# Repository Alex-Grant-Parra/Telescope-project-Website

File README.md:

# SELENO - Automated Sidereal Tracking and Remote Astronomy

## A modern telescope automation system for remote observation, object tracking and astrophotography with a web-based observatory management platform.

---

## Features

* Web-based telescope control  
* Distributed telescope network management  
* Automated target acquisition and tracking  
* Astrophotography image capture  
* Observation scheduling and automation  
* Interactive planetarium interface  
* Astronomical object database  
* Solar system object tracking  
* Remote camera and mount control  
* REST API for astronomical data access  
* Raspberry Pi and ESP32 powered telescope nodes  
* Beginner-friendly operation with advanced manual controls  
* Source-available and self-hostable

## System Architecture

SELENO uses a web-based control server connected to distributed Raspberry Pi \+ ESP32 telescope nodes. Commands, live view camera frames, and tracking data flow through WebSocket channels, while each node handles its own motor control, sensors, and imaging pipeline.

## Client Setup (For running SELENO on your telescope system)

* In the email you were sent when you purchased the telescope system, select register. This will give you a client ID, API token and server URL.  
* Create an account, and link your client ID and API key to it, following the on screen directions.  
* Power on the system, and wait for the blue LED to stay constantly lit.  
* Use the keypad to enter in the client ID, API token and server URL. There will be an on screen confirmation when connected.  
* (Recommended) Check for updates in the settings window. This may take several minutes if updates are found. Do not power off your device.   
* Log in and access the main interface page. It is recommended that you follow the first time tutorial on how to use the site.

## ADVANCED - Server Setup (For running your own control server)

 * Follow this guide to learn how to do this:
 https://github.com/Alex-Grant-Parra/SELENO/wiki/Server-Setup-(For-running-your-own-control-server)

 ## Core Runtime Behavior

- Flask app boots from Server.py.
- Blueprints are auto-loaded from controllers/.
- SQLite database is stored at instance/Data.db.
- WebSocket services start with the app:
	- Command server: port 4000
	- LiveView server: port 8000
- Route list is auto-generated to templates/routes.txt at startup.

## Important Environment Variables

- FLASK_SECRET_KEY: Flask session secret
- ENCRYPTION_KEY: application encryption key
- FLASK_USE_SSL: enable Flask TLS mode (True/False)
- SSL_CERT_PATH, SSL_KEY_PATH: cert and key when FLASK_USE_SSL is enabled
- FLASK_SERVER_HOST, FLASK_SERVER_PORT: host/port display and overrides
- MAX_UPLOAD_BYTES: max upload size (default 128 MiB)
- WS_IP: WebSocket bind IP (default 0.0.0.0)
- WS_PING_INTERVAL, WS_PING_TIMEOUT: WebSocket keepalive settings
- TURNSTILE_SITE_KEY, TURNSTILE_SECRET_KEY: CAPTCHA support

## Planetary Models

SELENO includes a few different planetary models under the astrophysics folder, each with varying precision.
- V1_Keplarian is a traditional keplarian algorithm
- V2_VSOP87A is an iterative solution, taking the sum of a large number of orbital parameters
- V3_Helios is a custom N-body engine, with a local integrator and engine, with initial parameters provided by JPL SPICE data

## Notes

- instance/.env contains secrets and should not be committed.
- infrastructure/ contains deployment-related files and logs.
- When downloading the server, the database will not be included. This may change in future versions, but you will have to supply your own data for now.

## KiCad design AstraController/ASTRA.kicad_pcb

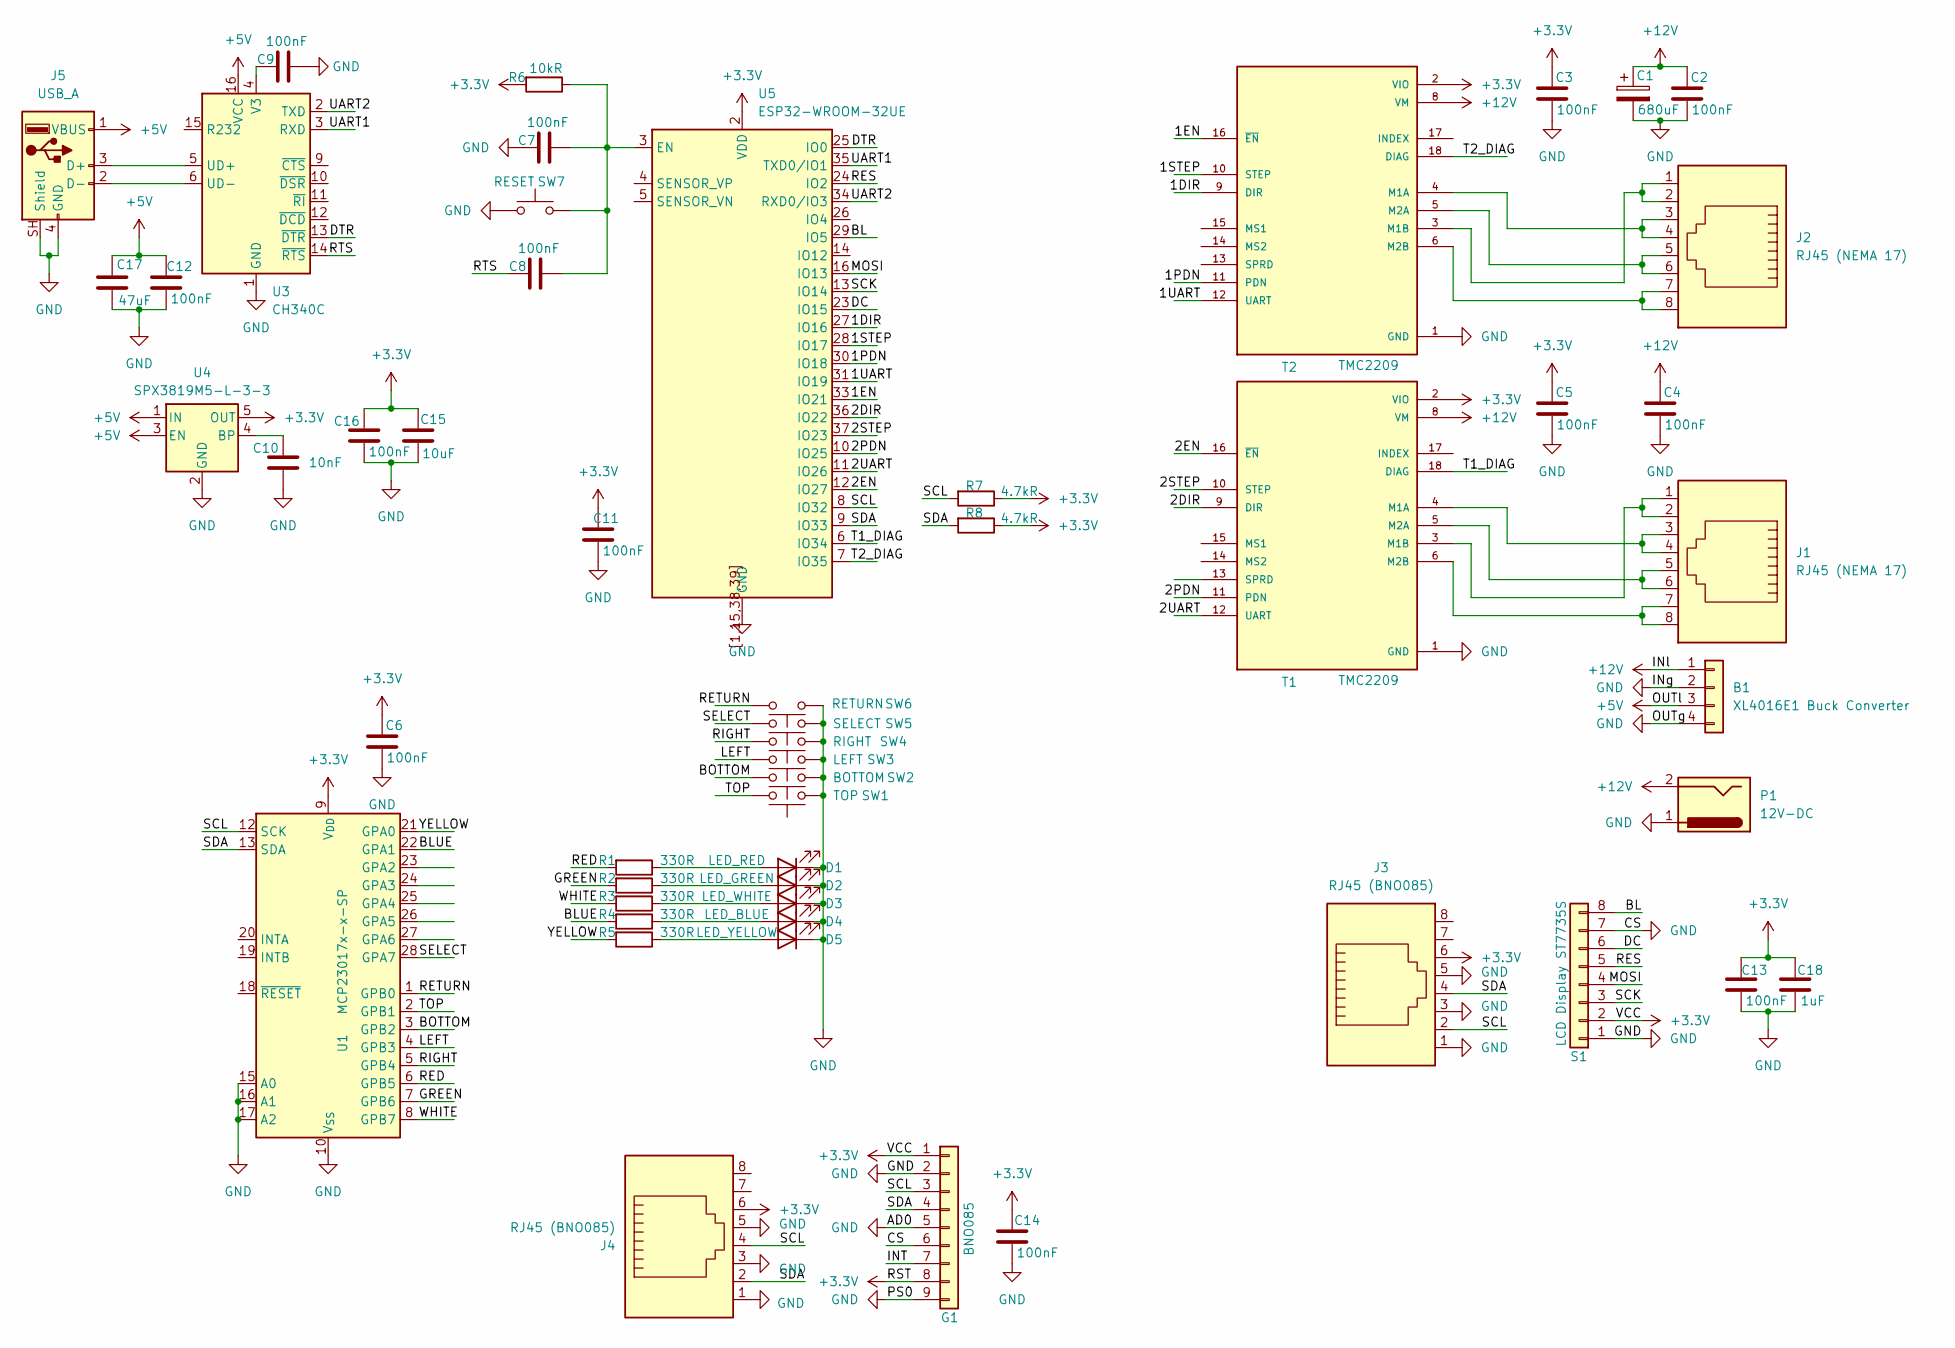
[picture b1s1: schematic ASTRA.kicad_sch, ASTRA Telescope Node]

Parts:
B1: XL4016E1 Buck Converter; Double 1x02 screw connector
C1: 680uF; CP_Radial_D10.0mm_P5.00mm
C2, C3, C4, C5, C6, C7, C8, C9, C11, C12, C13, C14, C16: 100nF; C_0402_1005Metric
C10: 10nF; C_0402_1005Metric
C15: 10uF; C_0402_1005Metric
C17: 47uF; C_1206_3216Metric
C18: 1uF; C_0402_1005Metric
D1: LED_RED; LED_0805_2012Metric
D2: LED_GREEN; LED_0805_2012Metric
D3: LED_WHITE; LED_0805_2012Metric
D4: LED_BLUE; LED_0805_2012Metric
D5: LED_YELLOW; LED_0805_2012Metric
G1: BNO085; PinSocket_1x09_P2.54mm_Vertical
J1, J2: RJ45 (NEMA 17); RJ45_Amphenol_54602-x08_Horizontal
J3, J4: RJ45 (BNO085); RJ45_Amphenol_54602-x08_Horizontal
J5: USB_A; USB_A_Connfly_DS1095
P1: 12V-DC; TerminalBlock_Xinya_XY308-2.54-2P_1x02_P2.54mm_Horizontal
R1, R2, R3, R4, R5: 330R; R_0402_1005Metric
R6: 10kR; R_0402_1005Metric
R7, R8: 4.7kR; R_0402_1005Metric
S1: LCD Display ST7735S; Quadruple 1x02 screw connector
SW1: TOP; TerminalBlock_Xinya_XY308-2.54-2P_1x02_P2.54mm_Horizontal
SW2: BOTTOM; TerminalBlock_Xinya_XY308-2.54-2P_1x02_P2.54mm_Horizontal
SW3: LEFT; TerminalBlock_Xinya_XY308-2.54-2P_1x02_P2.54mm_Horizontal
SW4: RIGHT; TerminalBlock_Xinya_XY308-2.54-2P_1x02_P2.54mm_Horizontal
SW5: SELECT; TerminalBlock_Xinya_XY308-2.54-2P_1x02_P2.54mm_Horizontal
SW6: RETURN; TerminalBlock_Xinya_XY308-2.54-2P_1x02_P2.54mm_Horizontal
SW7: RESET; TerminalBlock_Xinya_XY308-2.54-2P_1x02_P2.54mm_Horizontal
T1, T2: TMC2209; TMC2209module; PARTREV 1.20
U1: MCP23017x-x-SP; DIP-28_W7.62mm
U3: CH340C; SOIC-16_3.9x9.9mm_P1.27mm
U4: SPX3819M5-L-3-3; SOT-23-5; LCSC Part # C9055
U5: ESP32-WROOM-32UE

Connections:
+3.3V: C3.1, C5.1, C6.1, C11.1, C13.1, C14.1, C15.1, C16.1, C18.1, G1.1, G1.8, J3.6, J4.6, R6.2, R7.1, R8.1, S1.2, T1.2 (VIO), T2.2 (VIO), U1.9 (V_{DD}), U4.5 (OUT), U5.2 (VDD)
+5V: B1.3, C12.1, C17.1, J5.1 (VBUS), U3.16 (VCC), U4.1 (IN), U4.3 (EN)
+12V: B1.1, C1.1, C2.1, C4.1, P1.2, T1.8 (VM), T2.8 (VM)
/1DIR: T2.9 (DIR), U5.27 (IO16)
/1EN: T2.16 (~EN), U5.33 (IO21)
/1PDN: T2.11 (PDN), U5.30 (IO18)
/1STEP: T2.10 (STEP), U5.28 (IO17)
/1UART: T2.12 (UART), U5.31 (IO19)
/2DIR: T1.9 (DIR), U5.36 (IO22)
/2EN: T1.16 (~EN), U5.12 (IO27)
/2PDN: T1.11 (PDN), U5.10 (IO25)
/2STEP: T1.10 (STEP), U5.37 (IO23)
/2UART: T1.12 (UART), U5.11 (IO26)
/BL: S1.8, U5.29 (IO5)
/BLUE: R4.2, U1.22 (GPA1)
/BOTTOM: SW2.1, U1.3 (GPB2)
/DC: S1.6, U5.23 (IO15)
/DTR: U3.13 (~DTR), U5.25 (IO0)
/GREEN: R2.2, U1.7 (GPB6)
/LEFT: SW3.1, U1.4 (GPB3)
/MOSI: S1.4, U5.16 (IO13)
/RED: R1.2, U1.6 (GPB5)
/RES: S1.5, U5.24 (IO2)
/RETURN: SW6.1, U1.1 (GPB0)
/RIGHT: SW4.1, U1.5 (GPB4)
/RTS: C8.1, U3.14 (~RTS)
/SCK: S1.3, U5.13 (IO14)
/SCL: G1.3, J3.2, J4.4, R7.2, U1.12 (SCK), U5.8 (IO32)
/SDA: G1.4, J3.4, J4.2, R8.2, U1.13 (SDA), U5.9 (IO33)
/SELECT: SW5.1, U1.28 (GPA7)
/T1_DIAG: T1.18 (DIAG), U5.6 (IO34)
/T2_DIAG: T2.18 (DIAG), U5.7 (IO35)
/TOP: SW1.1, U1.2 (GPB1)
/UART1: U3.3 (RXD), U5.35 (TXD0/IO1)
/UART2: U3.2 (TXD), U5.34 (RXD0/IO3)
/WHITE: R3.2, U1.8 (GPB7)
/YELLOW: R5.2, U1.21 (GPA0)
GND: B1.2, B1.4, C1.2, C2.2, C3.2, C4.2, C5.2, C6.2, C7.1, C9.2, C10.2, C11.2, C12.2, C13.2, C14.2, C15.2, C16.2, C17.2, C18.2, D1.1 (K), D2.1 (K), D3.1 (K), D4.1 (K), D5.1 (K), G1.2, G1.5, G1.6, G1.9, J3.1, J3.3, J3.5, J4.1, J4.3, J4.5, J5.4 (GND), J5.SH (Shield), P1.1, S1.1, S1.7, SW1.2, SW2.2, SW3.2, SW4.2, SW5.2, SW6.2, SW7.1, T1.1 (GND), T1.7 (GND), T2.1 (GND), T2.7 (GND), U1.10 (V_{SS}), U1.15 (A0), U1.16 (A1), U1.17 (A2), U3.1 (GND), U4.2 (GND), U5.1 (GND), U5.15 (GND), U5.38 (GND), U5.39 (GND), U5.[1,15,38,39] (GND)
unnamed: D1.2 (A), R1.1
unnamed: D2.2 (A), R2.1
unnamed: D3.2 (A), R3.1
unnamed: D4.2 (A), R4.1
unnamed: D5.2 (A), R5.1
unnamed: J5.3 (D+), U3.5 (UD+)
unnamed: J5.2 (D-), U3.6 (UD-)
unnamed: J1.3, J1.4, T1.4 (M1A)
unnamed: J1.1, J1.2, T1.3 (M1B)
unnamed: J1.5, J1.6, T1.5 (M2A)
unnamed: J1.7, J1.8, T1.6 (M2B)
unnamed: J2.3, J2.4, T2.4 (M1A)
unnamed: J2.1, J2.2, T2.3 (M1B)
unnamed: J2.5, J2.6, T2.5 (M2A)
unnamed: J2.7, J2.8, T2.6 (M2B)
unnamed: C9.1, U3.4 (V3)
unnamed: C10.1, U4.4 (BP)
unnamed: C7.2, C8.2, R6.1, SW7.2, U5.3 (EN)

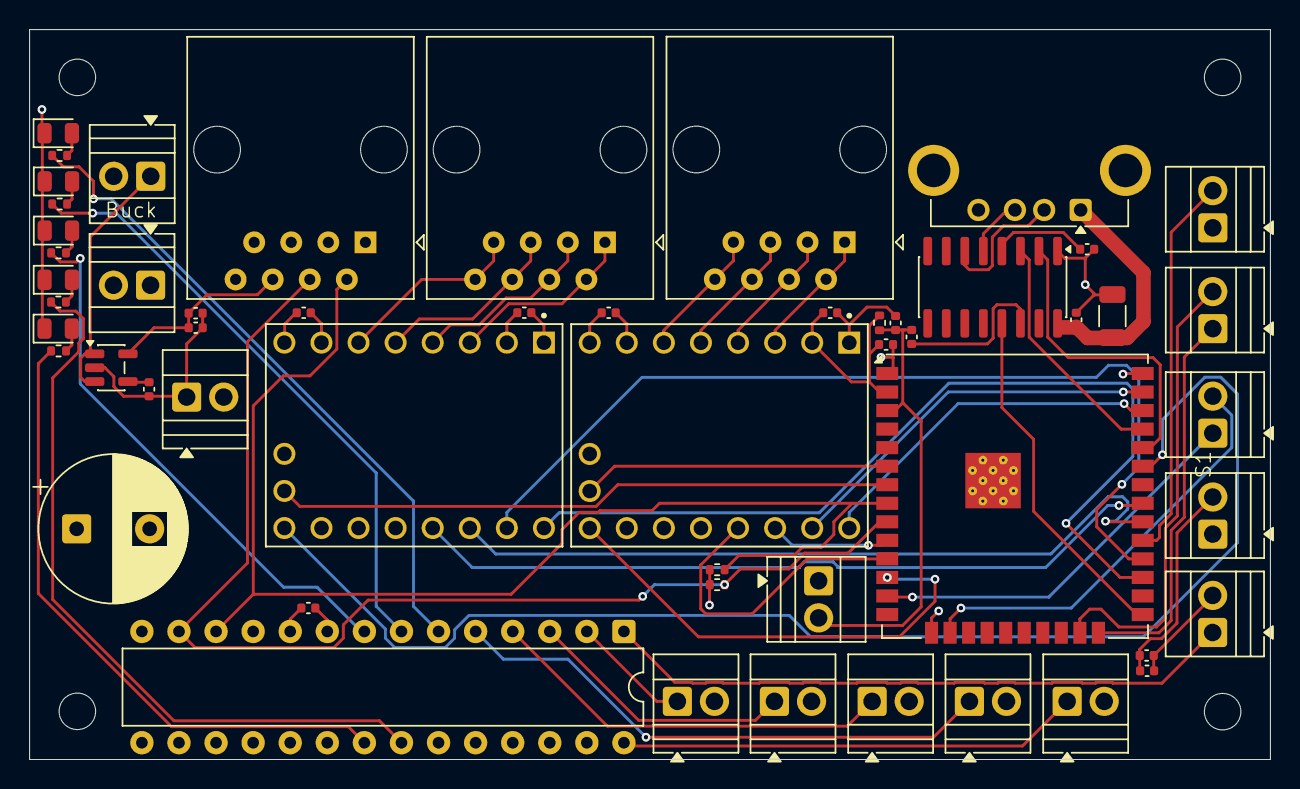
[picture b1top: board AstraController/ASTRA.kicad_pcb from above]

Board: 4 copper layers, 85.0 x 50.0 mm, 50 parts (0 on the bottom side), 56 nets.

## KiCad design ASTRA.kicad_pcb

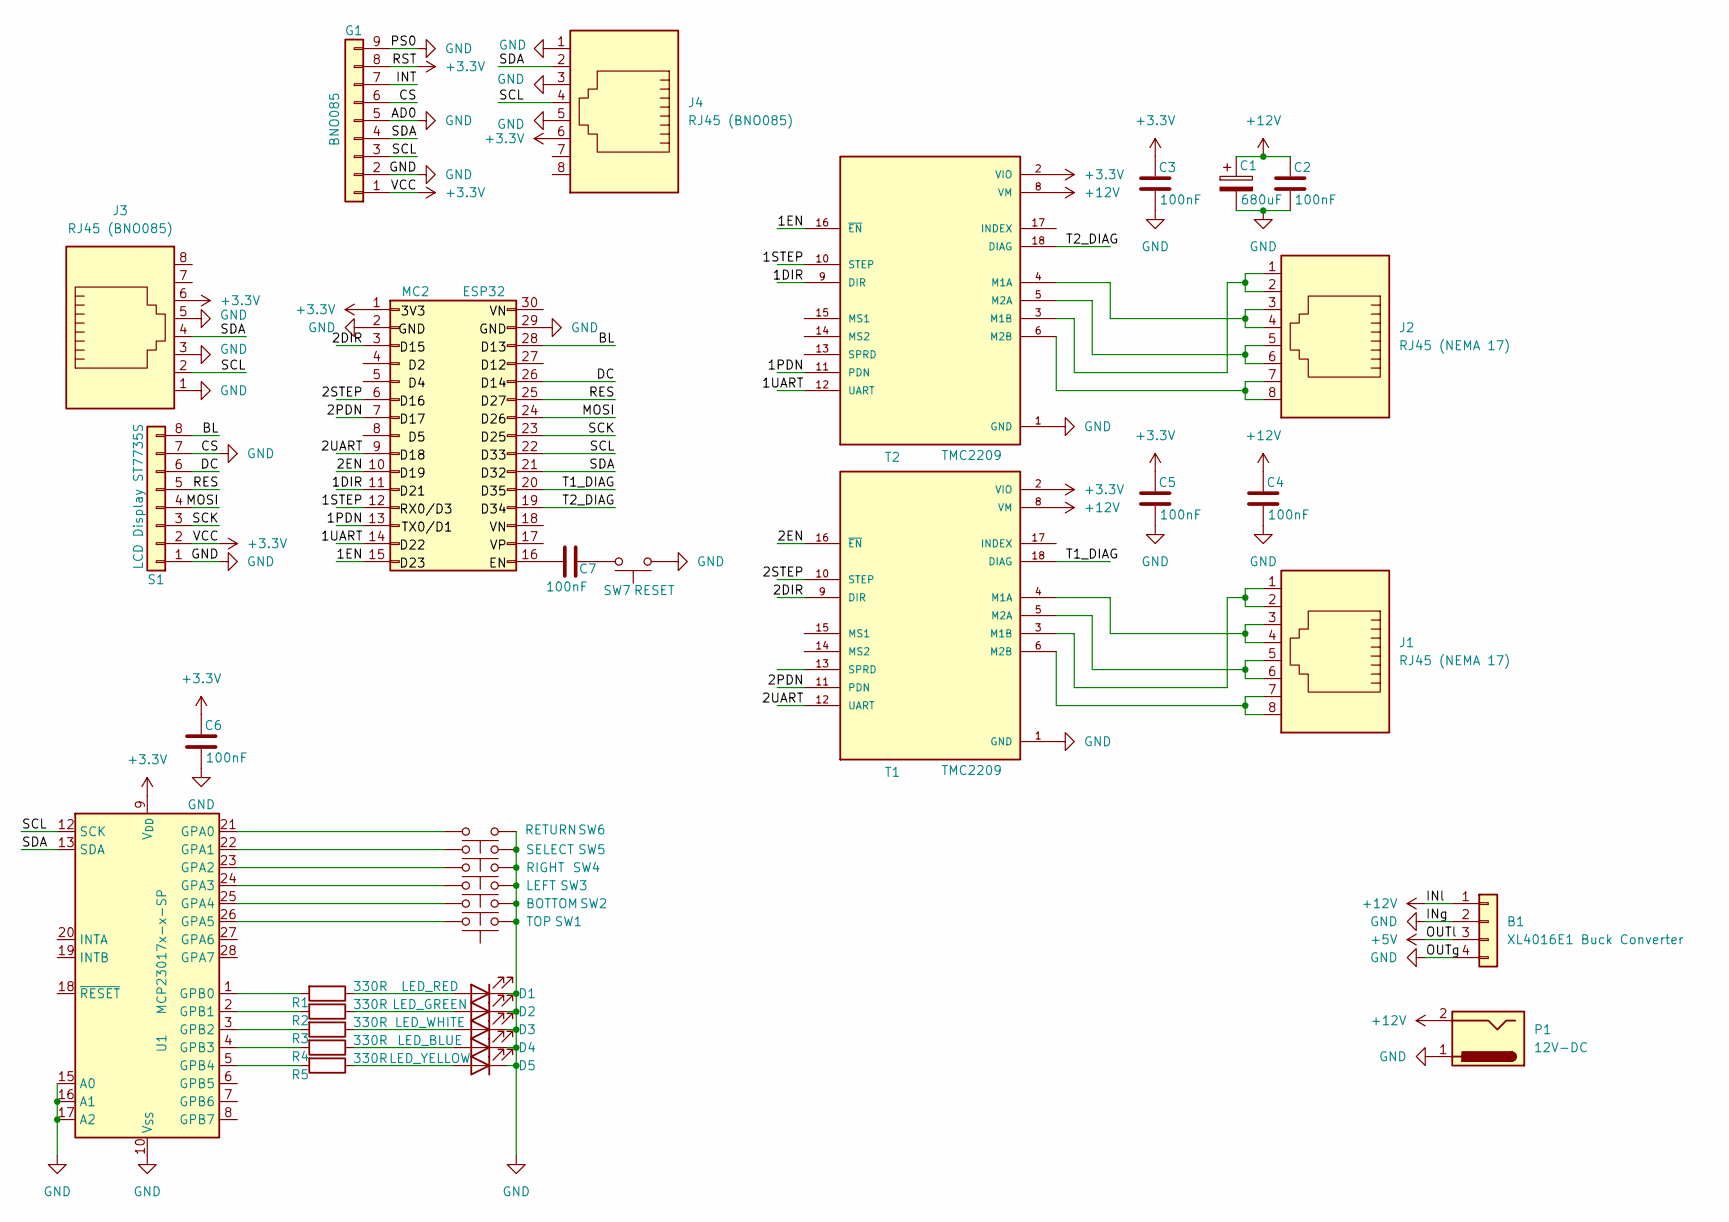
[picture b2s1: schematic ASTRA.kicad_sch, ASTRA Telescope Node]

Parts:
B1: XL4016E1 Buck Converter; PinSocket_1x04_P2.54mm_Vertical
C1: 680uF; CP_Radial_D8.0mm_P5.00mm
C2, C3, C4, C5, C6, C7: 100nF; C_Disc_D3.4mm_W2.1mm_P2.50mm
D1: LED_RED; LED_D5.0mm
D2: LED_GREEN; LED_D5.0mm
D3: LED_WHITE; LED_D5.0mm
D4: LED_BLUE; LED_D5.0mm
D5: LED_YELLOW; LED_D5.0mm
G1: BNO085; PinSocket_1x09_P2.54mm_Vertical
J1, J2: RJ45 (NEMA 17); RJ45_Amphenol_54602-x08_Horizontal
J3, J4: RJ45 (BNO085); RJ45_Amphenol_54602-x08_Horizontal
MC2: ESP32; ESP32-WROOM-32D-Devkit
P1: 12V-DC; PinSocket_1x03_P2.54mm_Vertical
R1, R2, R3, R4, R5: 330R; R_Axial_DIN0207_L6.3mm_D2.5mm_P2.54mm_Vertical
S1: LCD Display ST7735S; PinSocket_1x08_P2.54mm_Vertical
SW1: TOP; PinHeader_1x02_P2.54mm_Vertical
SW2: BOTTOM; PinHeader_1x02_P2.54mm_Vertical
SW3: LEFT; PinHeader_1x02_P2.54mm_Vertical
SW4: RIGHT; PinHeader_1x02_P2.54mm_Vertical
SW5: SELECT; PinHeader_1x02_P2.54mm_Vertical
SW6: RETURN; PinHeader_1x02_P2.54mm_Vertical
SW7: RESET; PinHeader_1x02_P2.54mm_Vertical
T1, T2: TMC2209; TMC2209module; PARTREV 1.20
U1: MCP23017x-x-SP; DIP-28_W7.62mm

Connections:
+3.3V: C3.1, C5.1, C6.1, G1.1, G1.8, J3.6, J4.6, MC2.1, S1.2, T1.2 (VIO), T2.2 (VIO), U1.9 (V_{DD})
+5V: B1.3
+12V: B1.1, C1.1, C2.1, C4.1, P1.2, T1.8 (VM), T2.8 (VM)
/1DIR: MC2.11 (Pin_21), T2.9 (DIR)
/1EN: MC2.15 (Pin_29), T2.16 (~EN)
/1PDN: MC2.13 (Pin_25), T2.11 (PDN)
/1STEP: MC2.12 (Pin_23), T2.10 (STEP)
/1UART: MC2.14 (Pin_27), T2.12 (UART)
/2DIR: MC2.3 (Pin_5), T1.9 (DIR)
/2EN: MC2.10 (Pin_19), T1.16 (~EN)
/2PDN: MC2.7 (Pin_13), T1.11 (PDN)
/2STEP: MC2.6 (Pin_11), T1.10 (STEP)
/2UART: MC2.9 (Pin_17), T1.12 (UART)
/BL: MC2.28 (Pin_6), S1.8
/DC: MC2.26 (Pin_10), S1.6
/MOSI: MC2.24 (Pin_14), S1.4
/RES: MC2.25 (Pin_12), S1.5
/SCK: MC2.23 (Pin_16), S1.3
/SCL: G1.3, J3.2, J4.4, MC2.22 (Pin_18), U1.12 (SCK)
/SDA: G1.4, J3.4, J4.2, MC2.21 (Pin_20), U1.13 (SDA)
/T1_DIAG: MC2.20 (Pin_22), T1.18 (DIAG)
/T2_DIAG: MC2.19 (Pin_24), T2.18 (DIAG)
GND: B1.2, B1.4, C1.2, C2.2, C3.2, C4.2, C5.2, C6.2, D1.1 (K), D2.1 (K), D3.1 (K), D4.1 (K), D5.1 (K), G1.2, G1.5, G1.6, G1.9, J3.1, J3.3, J3.5, J4.1, J4.3, J4.5, MC2.2 (Pin_3), MC2.29 (Pin_4), P1.1, S1.1, S1.7, SW1.2, SW2.2, SW3.2, SW4.2, SW5.2, SW6.2, SW7.1, T1.1 (GND), T1.7 (GND), T2.1 (GND), T2.7 (GND), U1.10 (V_{SS}), U1.15 (A0), U1.16 (A1), U1.17 (A2)
unnamed: C7.1, SW7.2
unnamed: D1.2 (A), R1.1
unnamed: D2.2 (A), R2.1
unnamed: D3.2 (A), R3.1
unnamed: D4.2 (A), R4.1
unnamed: D5.2 (A), R5.1
unnamed: C7.2, MC2.16 (Pin_30)
unnamed: J1.3, J1.4, T1.4 (M1A)
unnamed: J1.1, J1.2, T1.3 (M1B)
unnamed: J1.5, J1.6, T1.5 (M2A)
unnamed: J1.7, J1.8, T1.6 (M2B)
unnamed: J2.3, J2.4, T2.4 (M1A)
unnamed: J2.1, J2.2, T2.3 (M1B)
unnamed: J2.5, J2.6, T2.5 (M2A)
unnamed: J2.7, J2.8, T2.6 (M2B)
unnamed: SW6.1, U1.21 (GPA0)
unnamed: SW5.1, U1.22 (GPA1)
unnamed: SW4.1, U1.23 (GPA2)
unnamed: SW3.1, U1.24 (GPA3)
unnamed: SW2.1, U1.25 (GPA4)
unnamed: SW1.1, U1.26 (GPA5)
unnamed: R1.2, U1.1 (GPB0)
unnamed: R2.2, U1.2 (GPB1)
unnamed: R3.2, U1.3 (GPB2)
unnamed: R4.2, U1.4 (GPB3)
unnamed: R5.2, U1.5 (GPB4)

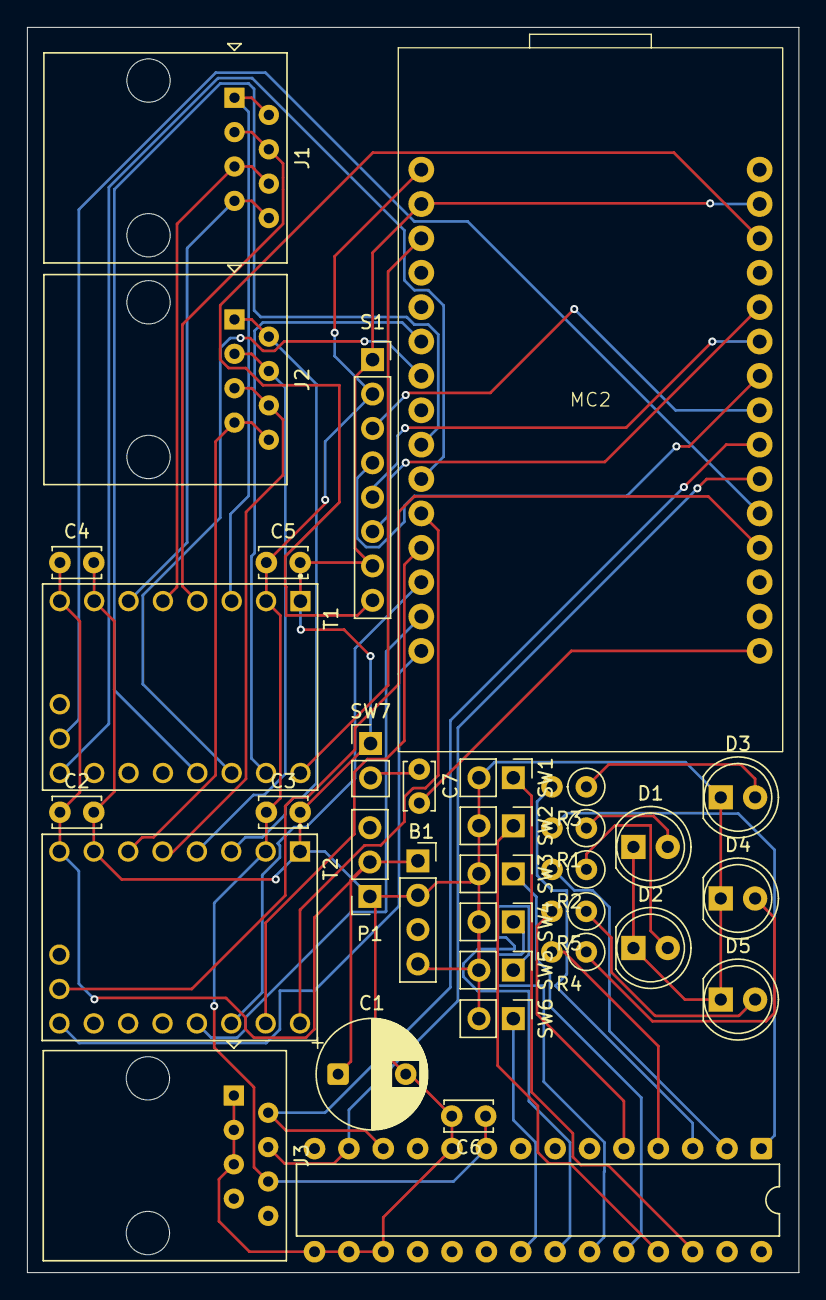
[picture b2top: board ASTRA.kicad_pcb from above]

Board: 2 copper layers, 57.0 x 92.0 mm, 34 parts (0 on the bottom side), 48 nets.

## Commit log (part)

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2025-09-25 Inside of sphere on star map (Not finished)
2025-09-25 Fixed star_map and correct projection
2025-09-25 correct star_map dragging mouse
2025-09-26 Add __pycache__ to .gitignore
2025-09-26 Planet sprites
2025-09-26 Right click to enter manual magnitude value
2025-09-26 qols
2025-09-26 Starts at mag4, and sets null mags to 50
2025-09-26 Grid lines (Half working)
2025-09-26 Common searching queries in interface and track button
2025-09-26 Added search function in star_map
2025-09-26 Security updates
2025-09-27 Requiring tokens for communication in WS
2025-09-27 Require tokens for auth to main WS
2025-09-27 upgraded from ws to wss
2025-09-27 Remove uncessecary commits
2025-09-27 Moved interface and star_map JS to dedicated files
2025-09-27 Converted DSOs to decimal degrees for RA
2025-09-29 Changed server url
2025-09-29 Fixed live view disconnect after time
2025-09-29 Update telescopeLink methods
2025-10-01 Togglable live view
2025-10-01 Toggleable live view
2025-10-01 Moving files :/
2025-10-02 Live view shown in interface
2025-10-06 Moved to waitress and removed unnecessary prints
2025-10-06 Branch temp
2025-10-10 csrf fixes
2025-10-10 csrf fixes 2
2025-10-10 fixed cloudflared.exe
2025-10-11 CSRF changes
2025-10-11 updating caddy file to wifi ip
2025-10-11 Peformance improvements to star_map
2025-10-11 Fixed rotation
2025-10-11 Fixed search and track issues
2025-10-11 Reorganising and README update
2025-10-11 Readme commit
2025-10-11 gitignore update
2025-10-11 Remove tracked __pycache__ files so .gitignore takes effect
2025-10-11 Apply .gitignore — remove cached files
2025-10-11 updated .gitignore
2025-10-12 Correct way around
2025-10-12 Inverted controlls
2025-10-12 Fixed toggle stars buttom
2025-10-12 Time
2025-10-12 temp
2025-10-13 Update README
    Removed warning about committing secrets and updated instructions for activating the virtual environment.
2025-10-13 Added and fixed time controls for star_map
2025-10-13 Auto install requirements
2025-10-13 Scrollover on star_map time
2025-10-13 Green grass bottom
2025-10-13 Removed lines behind camera
2025-10-13 star_map using stereographic coordinates
2025-10-13 Tiny timer script and fainter grass in star_map
2025-10-13 Refactor of time controls and moving planets
2025-10-13 Correct timing for planet locations + api work
2025-10-13 star_map optimisations
2025-10-13 ephemeris data added
2025-10-13 File moves
2025-10-13 Pickler added
2025-10-13 tests
2025-10-14 fix star_map
2025-10-14 working ephemeris (I think) for celestial coords
2025-10-14 Working precise ephemeris
2025-10-14 ephemeris finished
2025-10-17 Ported to python 3.9.5+
2025-10-19 movement
2025-10-20 Reset tokens
2025-10-20 Star search by common name
2025-10-20 Star map names for common names
2025-10-20 Fixed star lables for common names
2025-10-20 Time scrolling in star_map
2025-10-21 Redid homepage
2025-10-21 Fade
2025-10-21 crabNebula
2025-10-23 Faster video loading
2025-10-23 Esp32 controller (tests)
2025-10-23 bluetooth framework and reorganising
2025-10-27 Optimised star map for after first visit
2025-10-29 removing old files
2025-10-29 20th magnide limit on star_map
2025-10-29 Fixed bright stars missing
2025-10-29 Fixed trusted device login
2025-10-29 Dynamic telescope selection
2025-10-29 made reachable from local ips
2025-10-29 Work on contact
2025-10-29 Support mail server
2025-10-29 Better email colour
2025-10-29 Responding to support support_tickets
2025-10-30 Star map filtering and
2025-10-30 fix upload - still no date
2025-10-30 CSRF photo upload fixes
2025-10-30 Fixed album dates
2025-10-30 Deleting support tickets
2025-10-30 Ignore Data.db in future commits
2025-10-30 Track large files with Git LFS
2025-10-30 git add .gitattributes git commit -m "Stop tracking Data.db entirely"
2025-10-30 encryption of tickets
2025-10-31 CSRF
2025-11-09 Allowed local ip requests over HTTPS
2025-11-09 OOPed telescopeLink
2025-11-10 Manual tracking option
2025-11-25 Added manual motor controls to interface
2026-01-05 Work on motor control and star_map
2026-01-08 Planet finder using ephemeris and UX star_map updates
2026-01-10 Star map automatic zoom
2026-01-10 .env domain updates
2026-01-10 migrated to rpi02
2026-02-03 Linux
2026-02-03 Revert "Linux"
    This reverts commit 28af640eec9f29f13d67a00a3ebdb408b86f2f7c.
2026-02-03 remove ifonline
2026-02-03 Stop tracking static/videos
2026-02-07 json extraction
2026-02-07 various updates
2026-02-07 Fixed connected telescopes in interface and changed database schema for telescope ids
2026-02-07 Send tracking info to rpi client
2026-02-07 recieve tracking info from server
2026-02-07 Reorganised file structure and location getting
2026-02-08 Get hour angle and location
2026-02-08 First motor tracking alpha
2026-02-08 Downloads page
2026-02-08 legal stuff and rate limit
2026-02-08 Stopped liveview breaking
2026-02-15 New ESP32 firmware and interface for Rpi5 project.
2026-02-15 Async stop
2026-02-15 fix: remove tracking module and move functionality to hardware/tracking.py
2026-02-15 init motors
2026-02-15 Correct turning motion
2026-02-16 Camera state fixes
2026-02-16 Engage motor when using it automatically.
2026-02-16 position counter
2026-02-16 polar alignment check before tracking
2026-02-17 Motor waiting until turned
2026-02-17 Polling motor for wait until finished
2026-02-17 Handle negat
2026-02-17 camera lock
2026-02-17 Current RA and DEC
2026-02-17 Refined tracking
2026-02-17 Better tracking
2026-02-17 script an
2026-02-17 get telescope coords
2026-02-17 Location on star map and fixed interface info
2026-02-17 stopped redirect and 1 sec track with telescope
2026-02-18 favicon
2026-02-18 Prevent code 422 spam
2026-02-18 Added permanant on mode for motor
2026-02-18 fixed tracking
2026-02-18 Fully fixed tracking
2026-02-18 Tracking info in star map
2026-02-22 Rotating star map to match the current time (in sec)
2026-02-22 reverted moon finder to old algorithm
2026-02-26 updated to better handle slewing
2026-02-26 allow motors to go over AZ=0
2026-02-28 Rename project to ASTRA and update description
    Updated project name and description in README.
2026-03-01 websocket contact security
2026-03-01 More security
2026-03-01 time out and bug fix
2026-03-01 fix tuple bug
2026-03-02 allowed users to submit attachment different times
2026-03-02 Implememente CAPTCHA verification for key areas
2026-03-02 Multi Change state in admin control panel for contact us
2026-03-03 Fix changing account type
2026-03-08 removed plateSolver
2026-03-09 added supported cameras list in about
2026-03-12 updated ephemeris to use better naming and cleanup
2026-03-12 Matrix conversions
2026-03-12 Better utils
2026-03-12 Small cleanup
2026-03-12 more cleanup
2026-03-14 Initial plan
2026-03-14 Add ASTRA main server data flow diagram (draw.io XML)
2026-03-15 correct pins for motor2
2026-03-17 cleaned telescope link.py and websocket server.py
2026-03-17 cleaned controllers
2026-03-17 Cleaned algorithms
2026-03-17 Cleaned models
2026-03-17 Cleanup Security
2026-03-26 Must acce
2026-04-02 Logging in DB
2026-04-03 wiki and license
2026-04-03 Update copyright name in license file
2026-04-03 Update author name in license document
2026-04-04 requirements update
2026-04-04 Updated and improved JSON structure
2026-04-04 Better README
2026-04-04 Cleaned client code for package
2026-04-04 Bette README
2026-04-05 Fixed dodgy JSON
2026-04-11 Client downloads added to gitignore
2026-04-11 Updated TOS and license
2026-04-11 style updates
2026-04-11 Fixed bug where RA and DEC read as None if client is not set up
2026-04-11 QUICK_SETUP
2026-04-11 Allowing new versions to be sent to the main server
2026-04-12 Fixed developers not appearing online
2026-04-30 Remove dfd
2026-04-30 Placeholders for processing pagr
2026-04-30 image metadata visible
2026-04-30 Fixed image selection
2026-05-01 locationWorker + map improvements
2026-05-03 map improvements
2026-05-04 re add dev env for esp32
2026-05-04 esp32 led test script
2026-05-04 LED Controller in python
2026-05-04 fix depreciation warning
2026-05-04 remove testing file
2026-05-04 LED status integration into the project
2026-05-04 Fix token deletion
2026-05-05 Reorganised ESP32 firmware
2026-05-06 Auto reconnect esp32 when disconnected.
2026-05-09 readded rate limits
2026-05-09 Reorganised algorithms folder into Astrophysics
2026-05-09 New Helios calculator work
2026-05-09 Fixed
2026-05-09 gitignore to remove initial conditions
2026-05-09 Phase 2 integrator and engine for helios
2026-05-09 Fixed engine and added diagnostics
2026-05-09 Fixed integrator and engine + tests
2026-05-09 Remove plot_diagnostics
2026-05-09 v3 Astrophysics convert
2026-05-09 simplification
2026-05-11 Fixed bortle scale in maps
2026-05-11 Refreshes ESP32 connection
2026-05-11 display for esp32
2026-05-11 init
2026-05-11 Working display
2026-05-11 Remove Docstrings
2026-05-11 bugged graphics engine
2026-05-11 colours
2026-05-12 Map time
2026-05-12 colour
2026-05-12 a little frame progress
2026-05-12 Clear frame times
2026-05-12 fixed black scrolling
2026-05-12 plays gifs well
2026-05-12 better retry logic
2026-05-12 ESP32 display object uploader
2026-05-12 progress
2026-05-12 better preloading assets
2026-05-12 gif manager
2026-05-12 gif managers
2026-05-12 cleanup aux
2026-05-12 image image_display
2026-05-12 remove clear display after gif finished
2026-05-12 Asset playere
2026-05-12 smoother autoplay
2026-05-13 helper functions
2026-05-13 better helpers
2026-05-13 handle deleting gifs
2026-05-13 Check assets and connect to esp32 in runtime
2026-05-14 fix blue led
2026-05-14 Fixed blue led not turning off when disconnected
2026-05-14 fix tracking
2026-05-14 fix overwrite issue
2026-05-18 fix map issue
2026-05-30 Remove .history and ignore it
2026-05-30 Add gitignore
2026-05-31 added system Architecture diagram
2026-05-31 legality
2026-05-31 undo
2026-05-31 Ver 2
2026-06-06 V3 schematic
2026-06-07 Faster ESP32 error checking
2026-06-07 fix startup screen static
2026-06-11 V3 finished schem
2026-06-12 V4 hardware
2026-06-15 Much better admin interface for log viewing
2026-06-15 Fixed global flash issue
2026-06-15 Fixed profile dates and added backfill script for user created at field.
2026-06-15 temp work (a little broken)
2026-06-15 Added
2026-06-15 little booking
2026-06-15 Grid for bookings
2026-06-15 select up to date
2026-06-15 Redo fields in db
2026-06-15 light ram optimisations
2026-06-15 heavy ram optimisation
2026-06-16 Fixed telescope ips not properly shown
2026-06-16 Add packaging excludes to .gitignore
2026-06-16 mv Astrophysics to astrophysics
2026-06-16 Added a histogram to photos and interface live view
